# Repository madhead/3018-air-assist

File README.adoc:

= Automatic External Air Assist for 3018 CNCs

Some 3018 CNCs have a 12 V pin on the main board that can be used to control an air assist, such as https://www.sainsmart.com/collections/genmitsu-laser-upgrade-parts/products/genmitsu-air-assist-pump-kit-for-laser-engraver[this one].
However, you may already have an external air pump or a compressor that you can use as an air assist.
While you could operate it manually, it would be more convenient to have it turn on and off automatically with the laser, just like the original one.

This project aims to create an automatic air assist with an external air pump.

> ⚠️⚠️⚠️
> 
> This project assumes that your CNC has a motherboard with a 12 V / 0.6 A pin for the original air assist.
>
> Before proceeding, please:
>
> * Check your CNC's specifications to make sure it has the same pin.
> * Measure the voltage of the pin to confirm it's output.
> * If your CNC does not have the same pin or its voltage is different, you will need to adapt the scheme or you may not be able to use it at all.
>
> Always follow the common sense and safety rules.
> Project authors and contributors are not responsible for any damage or injury caused by this project.
>
> We're not going to speak about the laser hazards here, as you must already know (and follow) them if you're reading this.
>
> ⚠️⚡💥👀🤕😫🏥🦽

== Checking your CNC
== Circuit diagram 
== BOM
== Making a PCB
== Making a case

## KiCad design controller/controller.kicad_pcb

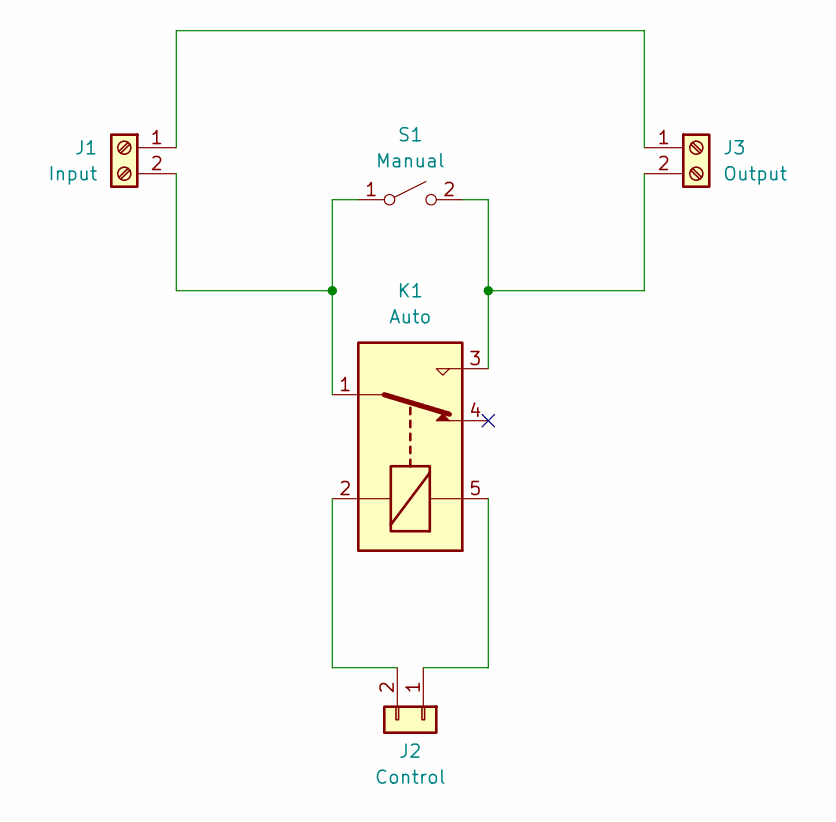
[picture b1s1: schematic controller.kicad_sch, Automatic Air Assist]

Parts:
J1: Input; TerminalBlock_bornier-2_P5.08mm
J2: Control; JST_XH_B2B-XH-A_1x02_P2.50mm_Vertical
J3: Output; TerminalBlock_bornier-2_P5.08mm
K1: Auto; Relay_SPDT_SANYOU_SRD_Series_Form_C
S1: Manual; TerminalBlock_bornier-2_P5.08mm

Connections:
unnamed: J1.1, J3.1
unnamed: J1.2, K1.1, S1.1 (A)
unnamed: J2.1, K1.5
unnamed: J2.2, K1.2
unnamed: J3.2, K1.3, S1.2 (B)

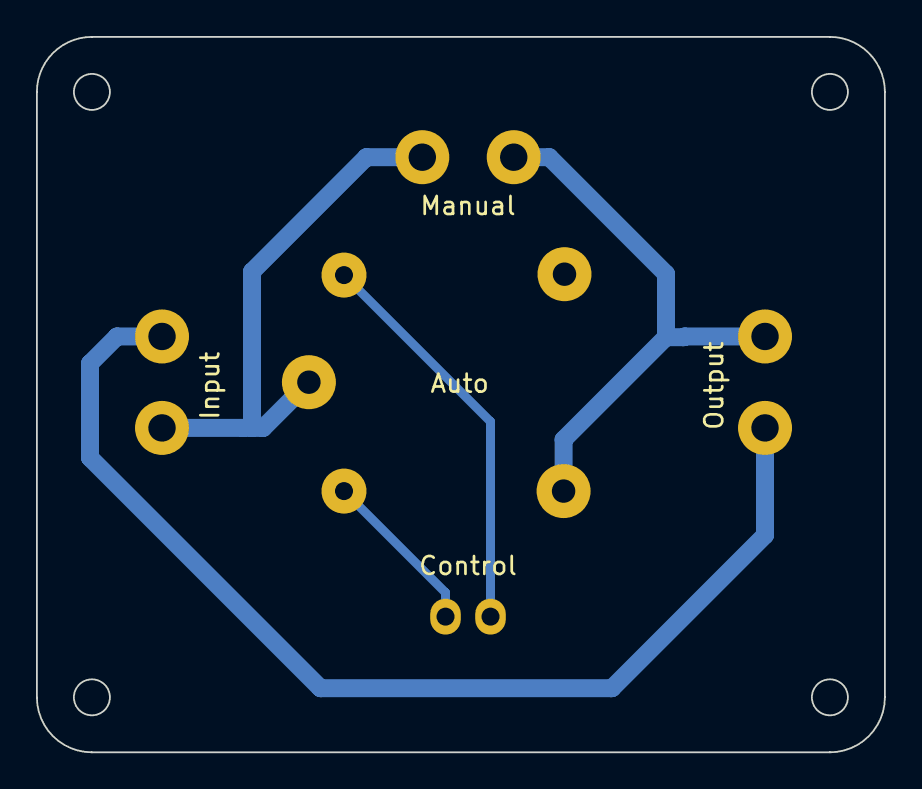
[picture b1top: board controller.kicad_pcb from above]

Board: 2 copper layers, 47.1 x 39.7 mm, 5 parts (0 on the bottom side), 5 nets.

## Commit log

2023-09-11 Init the project
2024-03-08 Update the controller schematics
2024-03-08 Controller rev. 2 (single output)
